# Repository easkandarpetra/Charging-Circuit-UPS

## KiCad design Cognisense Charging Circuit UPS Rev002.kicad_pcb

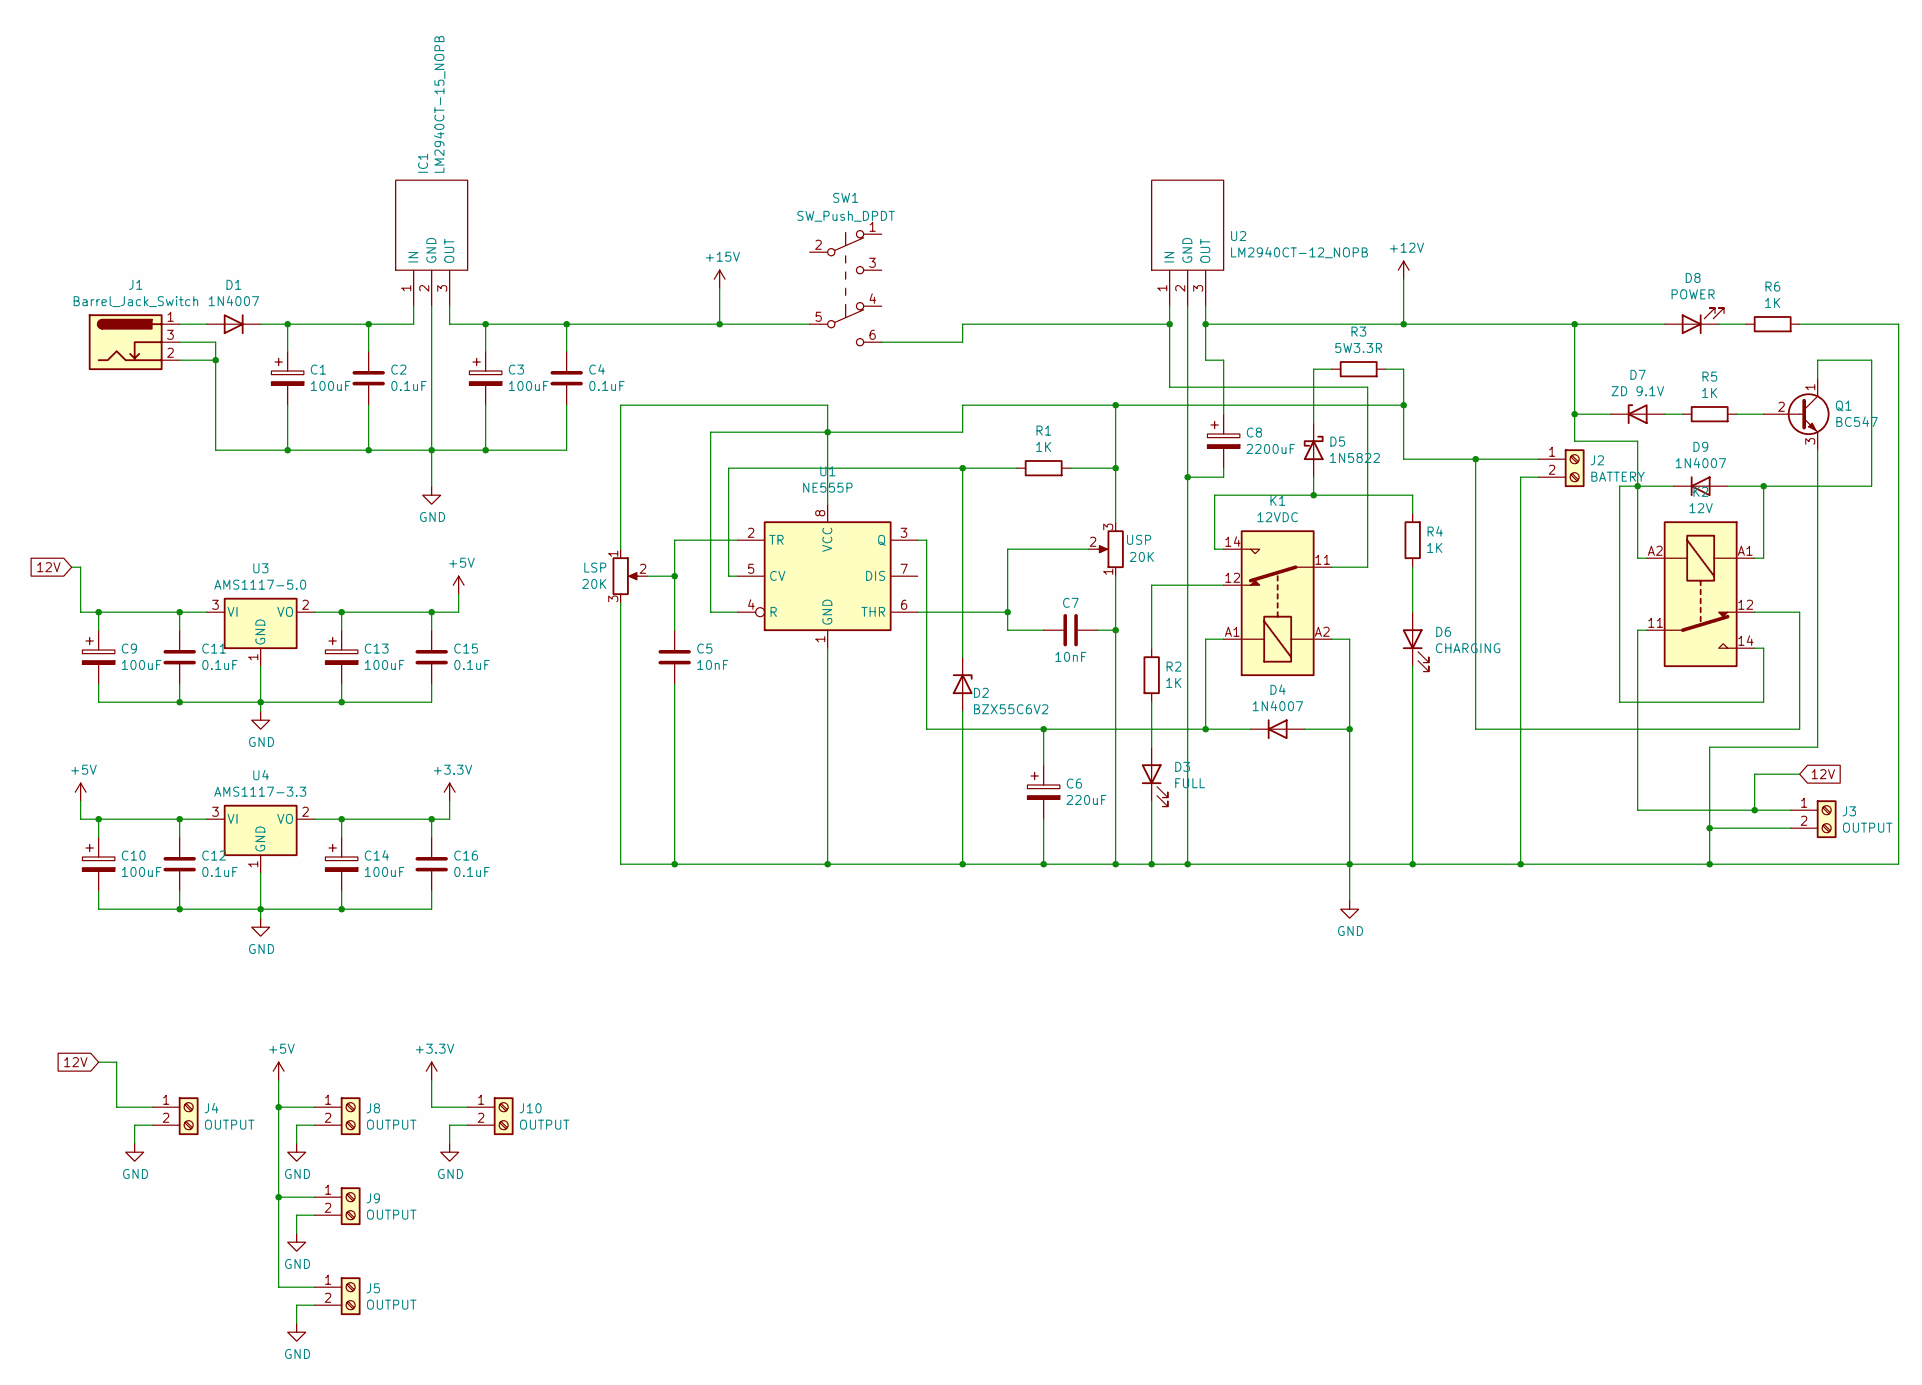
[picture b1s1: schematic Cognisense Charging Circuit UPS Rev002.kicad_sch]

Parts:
C1, C3, C9, C10, C13, C14: 100uF; C_Radial_D5.0mm_H7.0mm_P2.00mm
C2, C4, C11, C12, C15, C16: 0.1uF; C_Disc_D5.0mm_W2.5mm_P5.00mm
C5, C7: 10nF; C_Disc_D5.0mm_W2.5mm_P5.00mm
C6: 220uF; CP_Radial_D8.0mm_P2.50mm
C8: 2200uF; C_Radial_D12.5mm_H25.0mm_P5.00mm
D1, D4, D9: 1N4007; D_DO-41_SOD81_P7.62mm_Horizontal
D2: BZX55C6V2; D_DO-35_SOD27_P7.62mm_Horizontal
D3: FULL; LED_D5.0mm
D5: 1N5822; D_DO-201AD_P12.70mm_Horizontal
D6: CHARGING; LED_D5.0mm
D7: ZD 9.1V; D_DO-35_SOD27_P10.16mm_Horizontal
D8: POWER; LED_D5.0mm
IC1: LM2940CT-15_NOPB; TO-220-3_Vertical; Manufacturer_Part_Number LM2940CT-15/NOPB; Mouser Part Number 926-LM2940CT-15/NOPB
J1: Barrel_Jack_Switch; BarrelJack_Horizontal
J2: BATTERY; TerminalBlock_Phoenix_MKDS-1,5-2-5.08_1x02_P5.08mm_Horizont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
J3, J4, J5, J8, J9, J10: OUTPUT; TerminalBlock_Phoenix_MKDS-1,5-2-5.08_1x02_P5.08mm_Horizont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
K1: 12VDC; Relay_SPDT_Finder_36.11
K2: 12V; Relay_SPDT_Finder_36.11
LSP: 20K; Potentiometer_Bourns_3296W_Vertical
Q1: BC547; TO-92_Inline_Wide
R1, R2, R4, R5, R6: 1K; R_Axial_DIN0207_L6.3mm_D2.5mm_P7.62mm_Horizontal
R3: 5W3.3R; R_Axial_Power_L20.0mm_W6.4mm_P25.40mm
SW1: SW_Push_DPDT; SW_Push_2P2T_Toggle_CK_PVA2xxH1xxxxxxV2
U1: NE555P; DIP-8_W7.62mm_Socket
U2: LM2940CT-12_NOPB; TO-220-3_Vertical; Manufacturer_Part_Number LM2940CT-12/NOPB; Mouser Part Number 926-LM2940CT-12/NOPB
U3: AMS1117-5.0; TO-220-3_Vertical
U4: AMS1117-3.3; TO-220-3_Vertical
USP: 20K; Potentiometer_Bourns_3296W_Vertical

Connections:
12V: C9.1, C11.1, J3.1, J4.1, K2.11, U3.3 (VI)
+3V3: C14.1, C16.1, J10.1, U4.2 (VO)
+5V: C10.1, C12.1, C13.1, C15.1, J5.1, J8.1, J9.1, U3.2 (VO), U4.3 (VI)
+12V: C8.1, D7.1 (K), D8.2 (A), D9.1 (K), K2.14, K2.A2, U2.3 (OUT)
+15V: C3.1, C4.1, IC1.3 (OUT), SW1.5 (B)
GND: C1.2, C2.2, C3.2, C4.2, C5.2, C6.2, C7.1, C8.2, C9.2, C10.2, C11.2, C12.2, C13.2, C14.2, C15.2, C16.2, D2.2 (A), D3.1 (K), D4.2 (A), D6.1 (K), IC1.2 (GND), J1.2, J1.3, J2.2, J3.2, J4.2, J5.2, J8.2, J9.2, J10.2, K1.A2, LSP.3, Q1.3 (E), R6.2, U1.1 (GND), U2.2 (GND), U3.1 (GND), U4.1 (GND), USP.1
unnamed: C1.1, C2.1, D1.1 (K), IC1.1 (IN)
unnamed: C5.1, LSP.2, U1.2 (TR)
unnamed: C6.1, D4.1 (K), K1.A1, U1.3 (Q)
unnamed: C7.2, U1.6 (THR), USP.2
unnamed: D1.2 (A), J1.1
unnamed: D2.1 (K), R1.1, U1.5 (CV)
unnamed: D3.2 (A), R2.2
unnamed: D5.1 (K), R3.1
unnamed: D5.2 (A), K1.14, R4.2
unnamed: D6.2 (A), R4.1
unnamed: D7.2 (A), R5.1
unnamed: D8.1 (K), R6.1
unnamed: D9.2 (A), K2.A1, Q1.1 (C)
unnamed: J2.1, K2.12, LSP.1, R1.2, R3.2, U1.4 (R), U1.8 (VCC), USP.3
unnamed: K1.11, SW1.6 (C), U2.1 (IN)
unnamed: K1.12, R2.1
unnamed: Q1.2 (B), R5.2

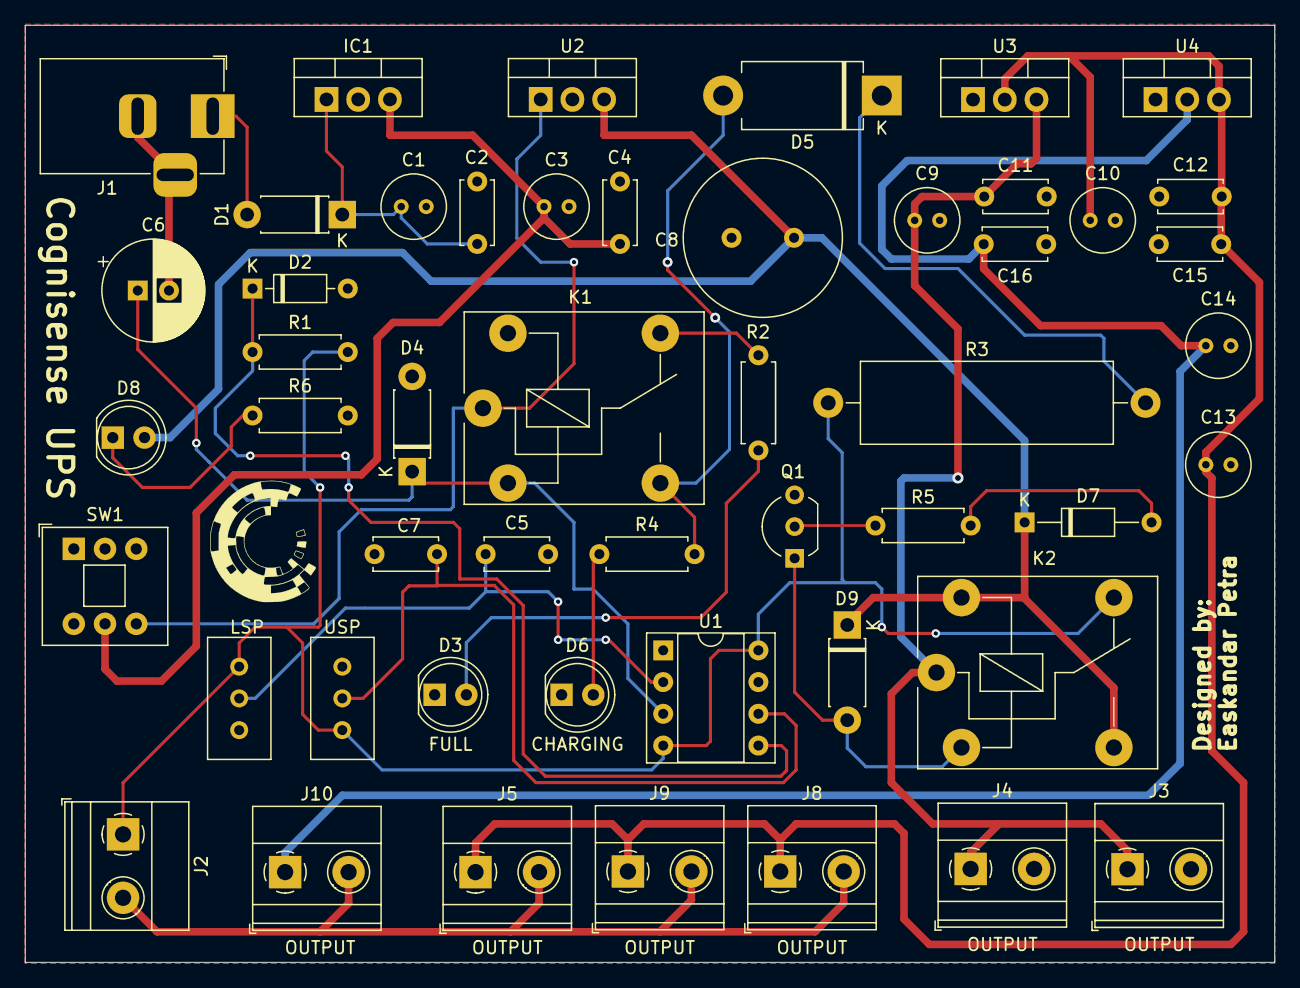
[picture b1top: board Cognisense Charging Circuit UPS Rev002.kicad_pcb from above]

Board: 2 copper layers, 100.0 x 75.0 mm, 50 parts (0 on the bottom side), 23 nets.

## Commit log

2022-04-13 Add updated circuit files
